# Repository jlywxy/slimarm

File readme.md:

# SlimARM Boards

The project is aiming to manufacture custom-made PCB of Embedded MPUs(most having ARM cores; specially-designed for specified usage, slim in dimension).<br>

Author: jlywxy(jlywxy@outlook.com)<br>
License: GPLv2<br>

- --

## Board List

<b>Important:</b><br>
Check `board/readme.PCB_DESIGN_STATUS.md` before actual PCB manufacture process. <br>Use verified boards only.
<br>
<br>
Status of Working Boards:
Code|Chipset|Core<br>DRAM Clock|PCB Stack<br>EDA|Status
-|-|-|-|-
Hypericum|Allwinner A20|1.2GHz 2x Cortex-A7<br>400MHz(800Mbps) DDR3|4-layer<br>KiCad|✅final-pcb
Carambola|Atmel AT91SAM9G25|400MHz ARM926EJ-S<br>133MHz(266Mbps) DDR2|4-layer<br>KiCad|✅final-pcb
Apricot B|Samsung S3C2416X|400MHz ARM926EJ-S<br>133MHz(266Mbps) DDR2|4-layer<br>LCEDA|pcb-revision
Almond B|Samsung S3C2410|200MHz ARM920T<br>133MHz SDR|4-layer<br>KiCAD|pcb-revision
||||
Azalea|Rockchip RK3128|1.1GHz 4x Cortex-A7<br>533MHz(1066Mbps)DDR3|4-layer<br>Cadence|pre-sch
Clematis|Rockchip RK3188|1.1GHz 4x Cortex-A9<br>533MHz(1066Mbps)DDR3|4-layer<br>KiCad|pre-sch
|Cumquat<br>(*SlimMIPS)|MediaTek MT7620A|580MHz MIPS24KEc<br>192MHz(384Mbps) DDR2|4-layer<br>KiCAD & Cadence(two versions)|pre-sch

Project Pipeline: planning -> avail-analyse -> pre-sch -> pcb-fab-test(1-stage pcb) -> software-test  -> post-sch -> pcb-revision -> post-pcb-fab-test -> final-pcb -> post-software-test -> done

- --
## Lastest Information
(this column started tracking from 2023.5.14)
* `Carambola`(AT91SAM9G25) the second version of hardware released and under test. Note: The first version failed for the wrong tuning of DDR lines. @ 2023.5.14
* `Apricot`(S3C2416) hardware final design finished with version/revision `v1r0x205`, the software for this board is under development @ 2023.5.17
* `Almond Mini`(S3C2410) hardware final design finished with version/revision `v1r1x208` @ 2023.5.20
* `Carambola` turning into a stall state for the unclear DDR2 initialization procedures of atmel mpus. @ 2023.5.26
* `Apricot` pushed new hardware version v1r1, which fixed UDEV clock input line and added pad teardrops. @ 2023.5.27
* added new plan for `Oxalis Mini` @ 2023.5.27
* cut down project plan with existing working plan. @ 2023.5.28
* `Apricot`(S3C2416) hardware debug is done, DDR2 initialization is ok. Starting USB 2.0 HS and Linux software debug. @ 2023.6.2
* corrected `Apricot` ddr clock information in project progress chart to 133 MHz. @ 2023.6.2
* dropped `Carambola`; starting `Oxalis Mini` schematic design. @ 2023.6.4
* revisioning `Carambola`; starting `Hypericum`. @ 2023.6.24
* `Hypericum`(a alias of `Oxalis Mini`)(Allwinner-A20) first board test done, revisioning; `Apricot`(S3C2416) third board(v1r3) test done, revisioning; `Carambola` board under test. @ 2023.7.2
* Fixed SDIO pull-up problem for `Hypericum`, `Carambola`, `Apricot` boards. @ 2023.7.11
* `Carambola` newest board tested done; needed to roll back to version that did not pulled up at SDIO, SAM9G25 have internal pull-up for SDIO.  @ 2023.7.15
* `Carambola`, `Hypericum` fixed with reset chip, SDIO pull-ups, ExtIO layout. These versions are verified and committed. @2023.7.22

## Misc
1. the version identifier on silkscreen of boards:<br>
(1)`v1r2e3` means version 1, revision 2, edition 3.<br>
typically written in `version 1.1.1`.<br>
(2)`v1r2x202` means version 1, revision 2, date May 14th.<br>
typically written in `version 1.1, 5.14`.<br>
these types of version identifiers are all used among boards.

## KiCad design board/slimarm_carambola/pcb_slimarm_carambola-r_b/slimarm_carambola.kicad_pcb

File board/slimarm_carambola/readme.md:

# SlimARM Carambola

## Recommended Software Test Procedure
1. DRAM test:<br>
* DDR controller set and DDR initialization.<br>
use AT91Bootstrap (version 3.x):<br>
(build binary)
```shell
$ cd /path/to/at91bootstrap/code
$ make mrproper
$ make core9g25-128m-nf_defconfig
$ CROSS_COMPILE=arm-none-eabi- make -j8
```
(do not use at91sam9x5ek configuration)
* DDR read/write stability test.<br>
use RAMStepper:<br>
(build binary)
```shell
$ cd /path/to/ramstepper
$ make clean
$ make carambola_config
```
this program writes to DDR SDRAM sequentially and reads out & compare data sequentially.

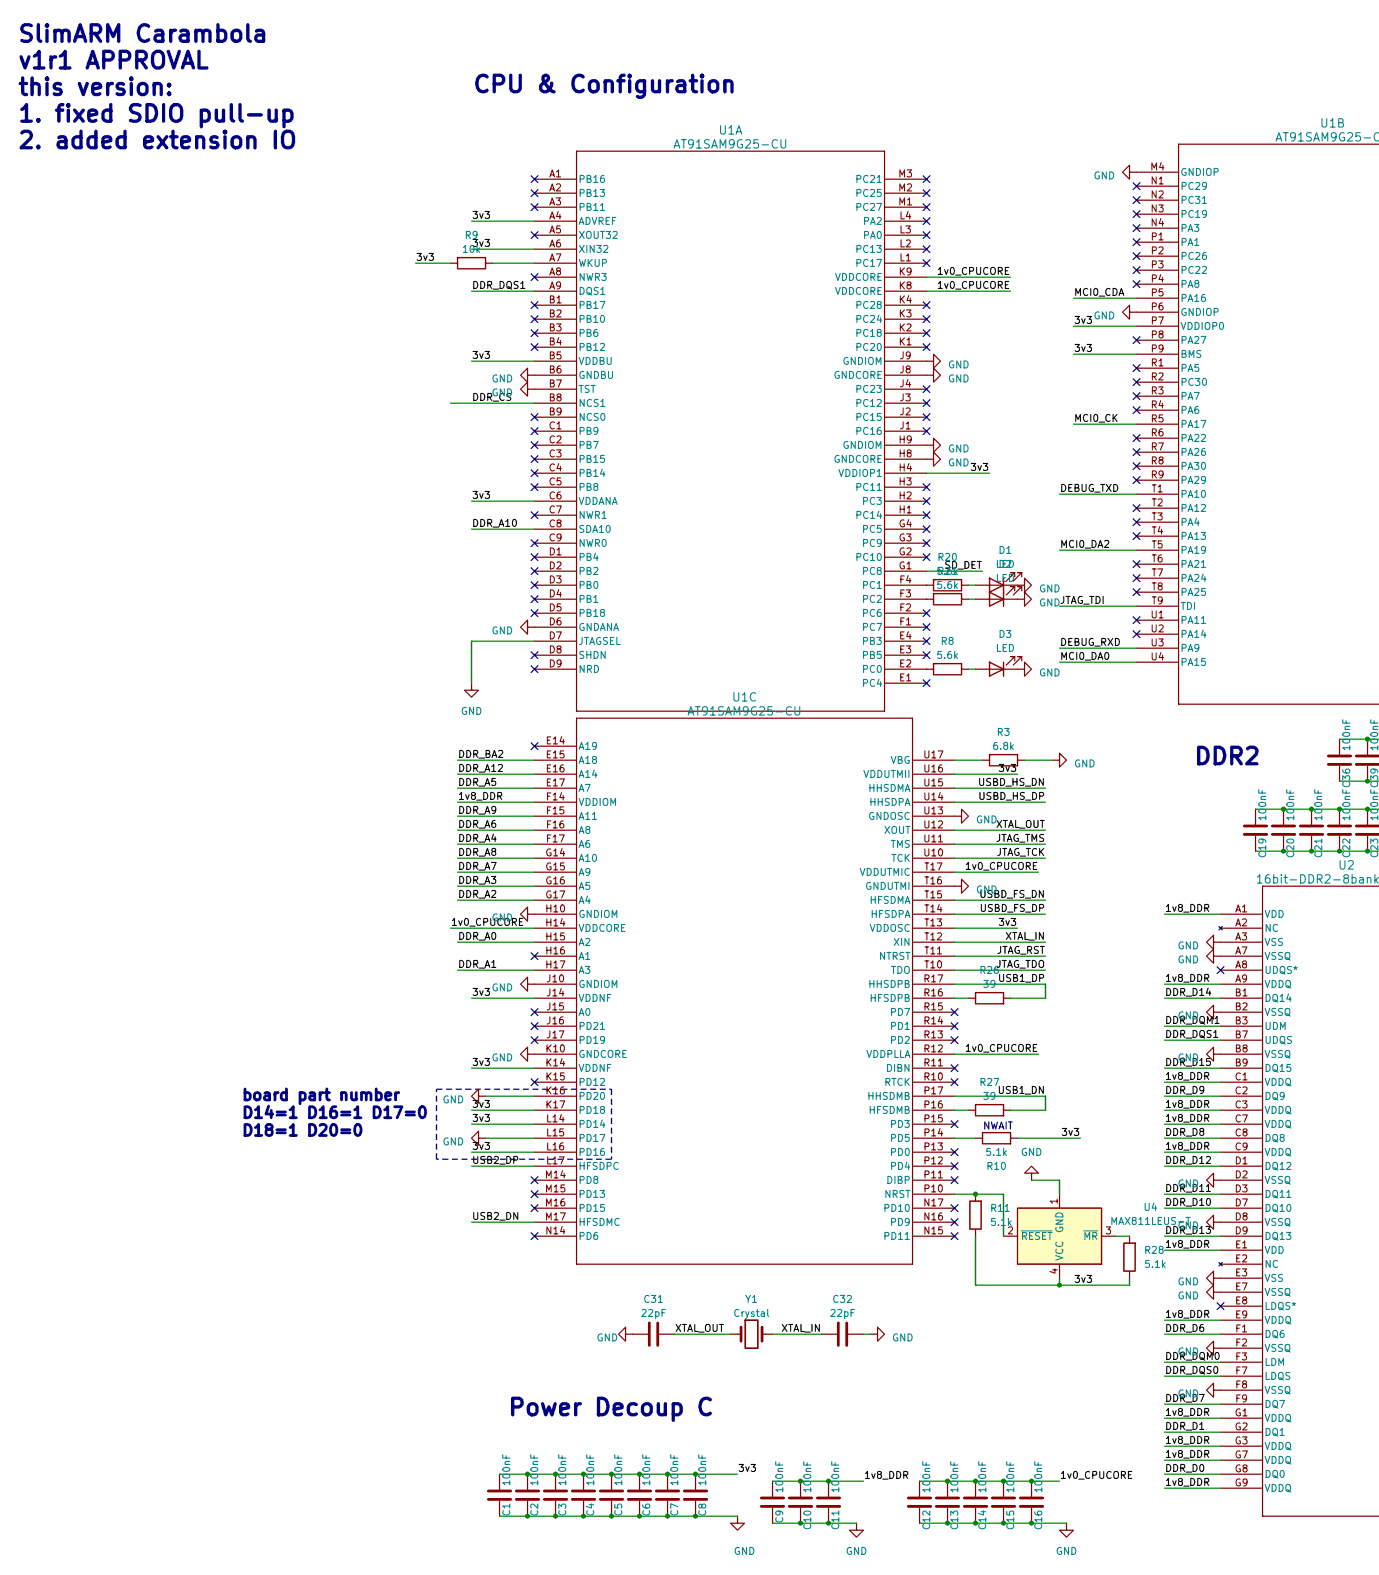
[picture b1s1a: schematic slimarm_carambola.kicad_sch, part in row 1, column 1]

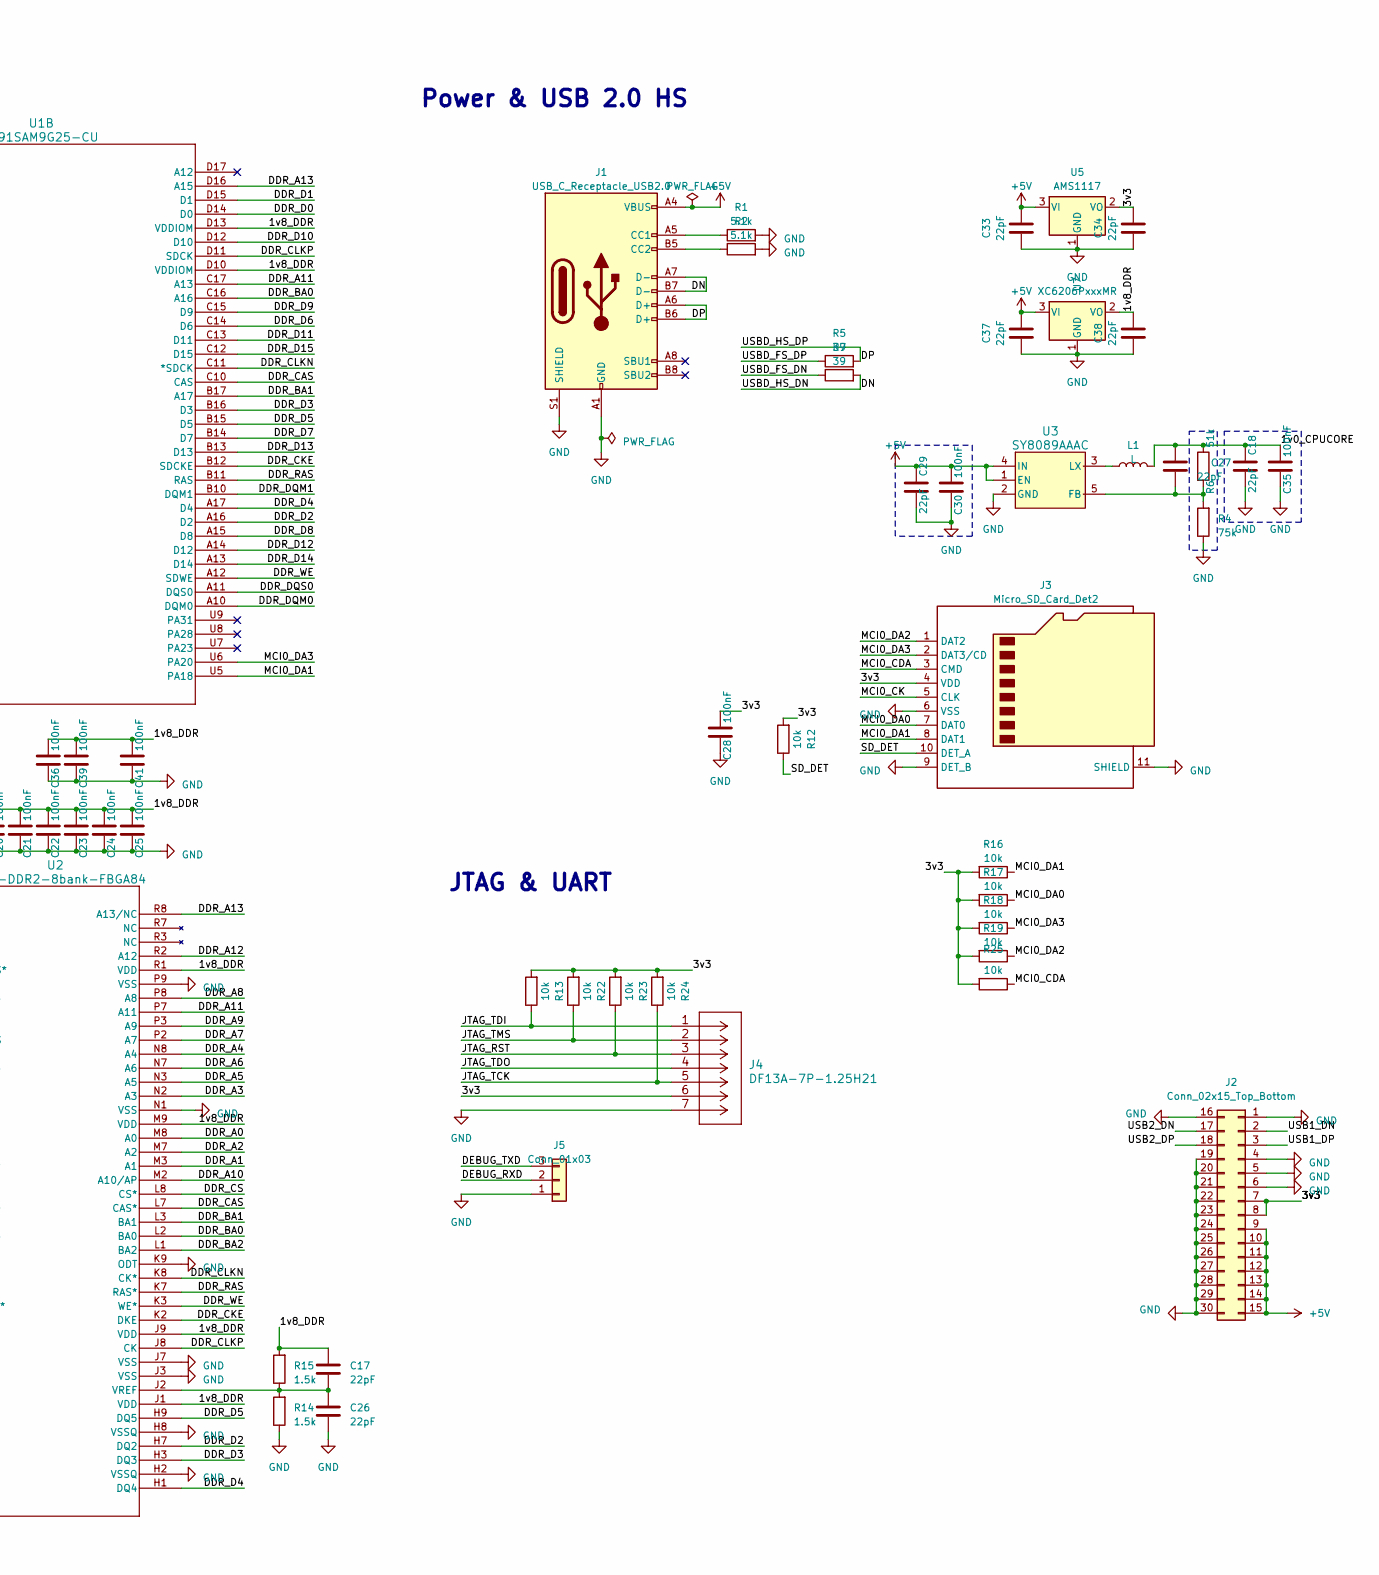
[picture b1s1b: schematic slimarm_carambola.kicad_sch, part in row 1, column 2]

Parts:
C1, C2, C3, C4, C5, C6, C7, C8, C9, C10, C11, C12, C13, C14, C15, C16, C19, C20, C21, C22, C23, C24, C25, C28, C30, C35, C36, C39, C41: 100nF; 0402
C17, C18, C26, C27, C29, C31, C32, C33, C34, C37, C38: 22pF; 0402
D1, D2, D3: LED; LED_0603_1608Metric_Pad1.05x0.95mm_HandSolder
J1: USB_C_Receptacle_USB2.0; USB_TYPEC_Receptacle
J2: Conn_02x15_Top_Bottom; Hirose_DF12_DF12E3.0-30DP-0.5V_2x15_P0.50mm_Vertical
J3: Micro_SD_Card_Det2; microSD_HC_Molex_104031-0811
J4: DF13A-7P-1.25H21
J5: Conn_01x03; PinHeader_1x03_P2.54mm_Vertical
L1: L; L_Sunlord_SWPA3015S
R1, R2, R10, R11, R28: 5.1k; 0402
R3: 6.8k; 0603
R4: 75k; 0603
R5, R7, R26, R27: 39; 0603
R6: 51k; 0603
R8, R20, R21: 5.6k; 0603
R9, R12, R13, R16, R17, R18, R19, R22, R23, R24, R25: 10k; 0402
R14, R15: 1.5k; 0603
U1: AT91SAM9G25-CU; AT91SAM9G25_JKT
U2: 16bit-DDR2-8bank-FBGA84; BGA84_DDR2
U3: SY8089AAAC; SY8089
U4: MAX811LEUS-T; SOT-143
U5: AMS1117; SOT-89-3
U7: XC6206PxxxMR; SOT-89-3
Y1: Crystal; Crystal_SMD_5032-2Pin_5.0x3.2mm

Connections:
+5V: C29.1, C30.2, C33.2, C37.2, J1.A4 (VBUS), J1.A9 (VBUS), J1.B4 (VBUS), J1.B9 (VBUS), J2.9, J2.10, J2.11, J2.12, J2.13, J2.14, J2.15, U3.1 (EN), U3.4 (IN), U5.3 (VI), U7.3 (VI)
/1v0_CPUCORE: C12.2, C13.2, C14.2, C15.2, C16.2, C18.1, C27.1, C35.2, L1.2, R6.1, U1.H14 (VDDCORE), U1.K8 (VDDCORE), U1.K9 (VDDCORE), U1.R12 (VDDPLLA), U1.T17 (VDDUTMIC)
/1v8_DDR: C9.2, C10.2, C11.2, C17.2, C19.2, C20.2, C21.2, C22.2, C23.2, C24.2, C25.2, C36.2, C38.2, C39.2, C41.2, R15.2, U1.D10 (VDDIOM), U1.D13 (VDDIOM), U1.F14 (VDDIOM), U2.A1 (VDD), U2.A9 (VDDQ), U2.C1 (VDDQ), U2.C3 (VDDQ), U2.C7 (VDDQ), U2.C9 (VDDQ), U2.E1 (VDD), U2.E9 (VDDQ), U2.G1 (VDDQ), U2.G3 (VDDQ), U2.G7 (VDDQ), U2.G9 (VDDQ), U2.J1 (VDD), U2.J9 (VDD), U2.M9 (VDD), U2.R1 (VDD), U7.2 (VO)
/3v3: C1.2, C2.2, C3.2, C4.2, C5.2, C6.2, C7.2, C8.2, C28.2, C34.2, J2.7, J2.8, J3.4 (VDD), J4.6, R9.2, R10.2, R11.1, R12.2, R13.2, R16.2, R17.2, R18.2, R19.2, R22.2, R23.2, R24.2, R25.2, R28.1, U1.A4 (ADVREF), U1.A6 (XIN32), U1.B5 (VDDBU), U1.C6 (VDDANA), U1.H4 (VDDIOP1), U1.J14 (VDDNF), U1.K14 (VDDNF), U1.K17 (PD18), U1.L14 (PD14), U1.L16 (PD16), U1.P7 (VDDIOP0), U1.P9 (BMS), U1.T13 (VDDOSC), U1.U16 (VDDUTMII), U4.4 (VCC), U5.2 (VO)
/DDR_A0: U1.H15 (A2), U2.M8 (A0)
/DDR_A1: U1.H17 (A3), U2.M3 (A1)
/DDR_A2: U1.G17 (A4), U2.M7 (A2)
/DDR_A3: U1.G16 (A5), U2.N2 (A3)
/DDR_A4: U1.F17 (A6), U2.N8 (A4)
/DDR_A5: U1.E17 (A7), U2.N3 (A5)
/DDR_A6: U1.F16 (A8), U2.N7 (A6)
/DDR_A7: U1.G15 (A9), U2.P2 (A7)
/DDR_A8: U1.G14 (A10), U2.P8 (A8)
/DDR_A9: U1.F15 (A11), U2.P3 (A9)
/DDR_A10: U1.C8 (SDA10), U2.M2 (A10/AP)
/DDR_A11: U1.C17 (A13), U2.P7 (A11)
/DDR_A12: U1.E16 (A14), U2.R2 (A12)
/DDR_A13: U1.D16 (A15), U2.R8 (A13/NC)
/DDR_BA0: U1.C16 (A16), U2.L2 (BA0)
/DDR_BA1: U1.B17 (A17), U2.L3 (BA1)
/DDR_BA2: U1.E15 (A18), U2.L1 (BA2)
/DDR_CAS: U1.C10 (CAS), U2.L7 (CAS*)
/DDR_CKE: U1.B12 (SDCKE), U2.K2 (DKE)
/DDR_CLKN: U1.C11 (*SDCK), U2.K8 (CK*)
/DDR_CLKP: U1.D11 (SDCK), U2.J8 (CK)
/DDR_CS: U1.B8 (NCS1), U2.L8 (CS*)
/DDR_D0: U1.D14 (D0), U2.G8 (DQ0)
/DDR_D1: U1.D15 (D1), U2.G2 (DQ1)
/DDR_D2: U1.A16 (D2), U2.H7 (DQ2)
/DDR_D3: U1.B16 (D3), U2.H3 (DQ3)
/DDR_D4: U1.A17 (D4), U2.H1 (DQ4)
/DDR_D5: U1.B15 (D5), U2.H9 (DQ5)
/DDR_D6: U1.C14 (D6), U2.F1 (DQ6)
/DDR_D7: U1.B14 (D7), U2.F9 (DQ7)
/DDR_D8: U1.A15 (D8), U2.C8 (DQ8)
/DDR_D9: U1.C15 (D9), U2.C2 (DQ9)
/DDR_D10: U1.D12 (D10), U2.D7 (DQ10)
/DDR_D11: U1.C13 (D11), U2.D3 (DQ11)
/DDR_D12: U1.A14 (D12), U2.D1 (DQ12)
/DDR_D13: U1.B13 (D13), U2.D9 (DQ13)
/DDR_D14: U1.A13 (D14), U2.B1 (DQ14)
/DDR_D15: U1.C12 (D15), U2.B9 (DQ15)
/DDR_DQM0: U1.A10 (DQM0), U2.F3 (LDM)
/DDR_DQM1: U1.B10 (DQM1), U2.B3 (UDM)
/DDR_DQS0: U1.A11 (DQS0), U2.F7 (LDQS)
/DDR_DQS1: U1.A9 (DQS1), U2.B7 (UDQS)
/DDR_RAS: U1.B11 (RAS), U2.K7 (RAS*)
/DDR_WE: U1.A12 (SDWE), U2.K3 (WE*)
/DEBUG_RXD: J5.2, U1.U3 (PA9)
/DEBUG_TXD: J5.3, U1.T1 (PA10)
/DN: J1.A7 (D-), J1.B7 (D-), R7.2, U1.U15 (HHSDMA)
/DP: J1.A6 (D+), J1.B6 (D+), R5.2, U1.U14 (HHSDPA)
/JTAG_RST: J4.3, R23.1, U1.T11 (NTRST)
/JTAG_TCK: J4.5, R24.1, U1.U10 (TCK)
/JTAG_TDI: J4.1, R13.1, U1.T9 (TDI)
/JTAG_TDO: J4.4, U1.T10 (TDO)
/JTAG_TMS: J4.2, R22.1, U1.U11 (TMS)
/MCI0_CDA: J3.3 (CMD), R25.1, U1.P5 (PA16)
/MCI0_CK: J3.5 (CLK), U1.R5 (PA17)
/MCI0_DA0: J3.7 (DAT0), R17.1, U1.U4 (PA15)
/MCI0_DA1: J3.8 (DAT1), R16.1, U1.U5 (PA18)
/MCI0_DA2: J3.1 (DAT2), R19.1, U1.T5 (PA19)
/MCI0_DA3: J3.2 (DAT3/CD), R18.1, U1.U6 (PA20)
/SD_DET: J3.10 (DET_A), R12.1, U1.G1 (PC8)
/USB1_DN: J2.2, R27.2, U1.P17 (HHSDMB)
/USB1_DP: J2.3, R26.2, U1.R17 (HHSDPB)
/USB2_DN: J2.17, U1.M17 (HFSDMC)
/USB2_DP: J2.18, U1.L17 (HFSDPC)
/USBD_FS_DN: R7.1, U1.T15 (HFSDMA)
/USBD_FS_DP: R5.1, U1.T14 (HFSDPA)
/XTAL_IN: C32.1, U1.T12 (XIN), Y1.2
/XTAL_OUT: C31.2, U1.U12 (XOUT), Y1.1
GND: C1.1, C2.1, C3.1, C4.1, C5.1, C6.1, C7.1, C8.1, C9.1, C10.1, C11.1, C12.1, C13.1, C14.1, C15.1, C16.1, C18.2, C19.1, C20.1, C21.1, C22.1, C23.1, C24.1, C25.1, C26.1, C28.1, C29.2, C30.1, C31.1, C32.2, C33.1, C34.1, C35.1, C36.1, C37.1, C38.1, C39.1, C41.1, D1.1 (K), D2.1 (K), D3.1 (K), J1.A1 (GND), J1.A12 (GND), J1.B1 (GND), J1.B12 (GND), J1.S1 (SHIELD), J2.1, J2.4, J2.5, J2.6, J2.16, J2.19, J2.20, J2.21, J2.22, J2.23, J2.24, J2.25, J2.26, J2.27, J2.28, J2.29, J2.30, J3.6 (VSS), J3.9 (DET_B), J3.11 (SHIELD), J4.7, J5.1, R1.2, R2.2, R3.1, R4.1, R14.1, U1.B6 (GNDBU), U1.B7 (TST), U1.D6 (GNDANA), U1.D7 (JTAGSEL), U1.H8 (GNDCORE), U1.H9 (GNDIOM), U1.H10 (GNDIOM), U1.J8 (GNDCORE), U1.J9 (GNDIOM), U1.J10 (GNDIOM), U1.K10 (GNDCORE), U1.K16 (PD20), U1.L15 (PD17), U1.M4 (GNDIOP), U1.P6 (GNDIOP), U1.T16 (GNDUTMI), U1.U13 (GNDOSC), U2.A3 (VSS), U2.A7 (VSSQ), U2.B2 (VSSQ), U2.B8 (VSSQ), U2.D2 (VSSQ), U2.D8 (VSSQ), U2.E3 (VSS), U2.E7 (VSSQ), U2.F2 (VSSQ), U2.F8 (VSSQ), U2.H2 (VSSQ), U2.H8 (VSSQ), U2.J3 (VSS), U2.J7 (VSS), U2.K9 (ODT), U2.N1 (VSS), U2.P9 (VSS), U3.2 (GND), U4.1 (GND), U5.1 (GND), U7.1 (GND)
unnamed: D1.2 (A), R20.1
unnamed: D2.2 (A), R21.1
unnamed: D3.2 (A), R8.1
unnamed: J1.A5 (CC1), R1.1
unnamed: J1.B5 (CC2), R2.1
unnamed: R8.2, U1.E2 (PC0)
unnamed: R20.2, U1.F4 (PC1)
unnamed: R21.2, U1.F3 (PC2)
unnamed: R9.1, U1.A7 (WKUP)
unnamed: R27.1, U1.P16 (HFSDMB)
unnamed: R26.1, U1.R16 (HFSDPB)
unnamed: R11.2, U1.P10 (NRST), U4.2 (~RESET)
unnamed: R10.1, U1.P14 (PD5)
unnamed: R3.2, U1.U17 (VBG)
unnamed: C17.1, C26.2, R14.2, R15.1, U2.J2 (VREF)
unnamed: C27.2, R4.2, R6.2, U3.5 (FB)
unnamed: L1.1, U3.3 (LX)
unnamed: R28.2, U4.3 (~MR)

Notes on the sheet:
CPU & Configuration
NWAIT
SlimARM Carambola v1r1 APPROVAL this version: 1. fixed SDIO pull-up 2. added extension IO
Power & USB 2.0 HS
JTAG & UART
DDR2
Power Decoup C
board part number D14=1 D16=1 D17=0 D18=1 D20=0

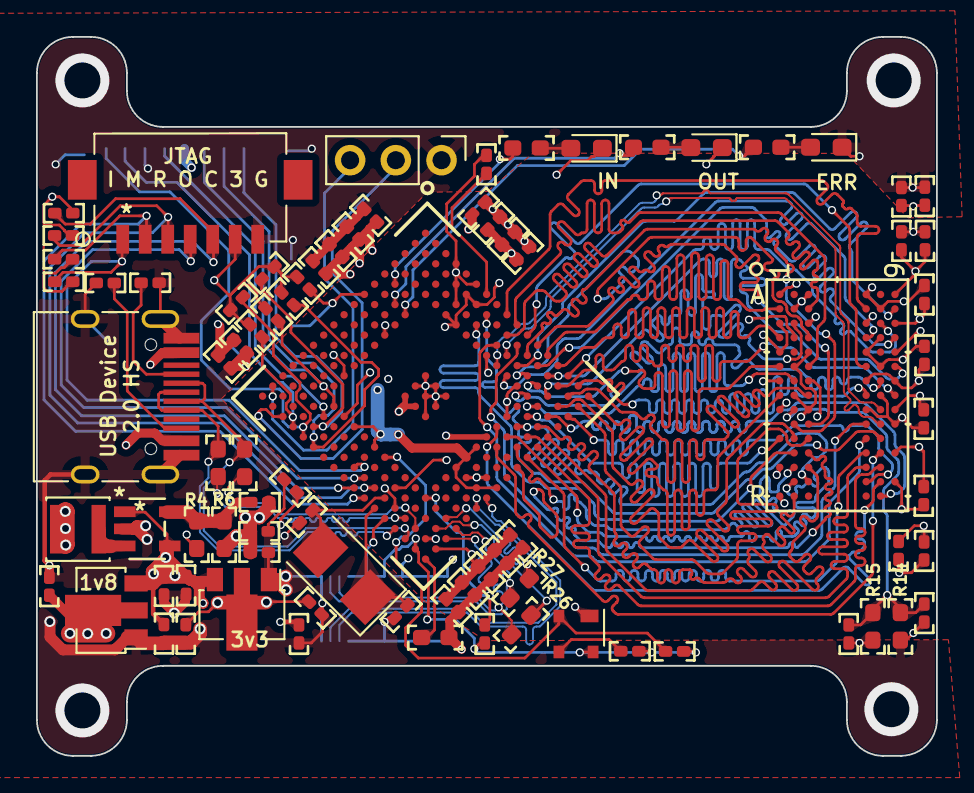
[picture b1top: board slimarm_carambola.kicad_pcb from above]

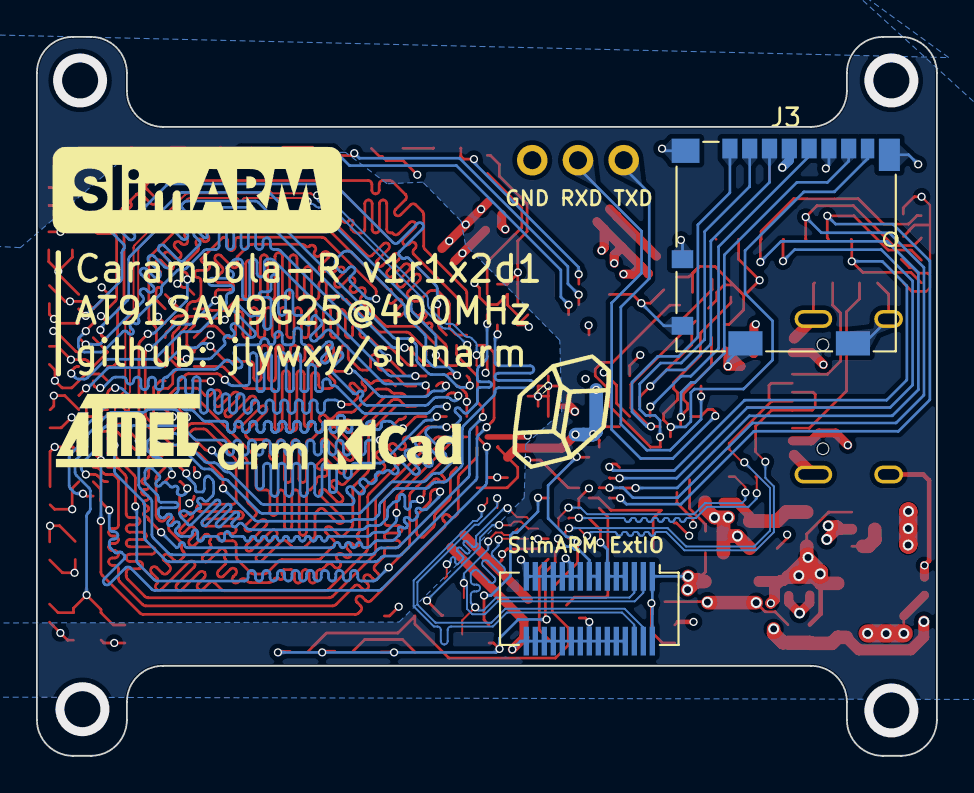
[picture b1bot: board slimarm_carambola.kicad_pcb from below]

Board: 4 copper layers, 50.0 x 39.9 mm, 84 parts (2 on the bottom side), 91 nets.

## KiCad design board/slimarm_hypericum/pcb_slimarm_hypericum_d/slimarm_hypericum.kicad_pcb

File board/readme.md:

# Boards

Project status:<br>
```
[ok]SlimARM Almond Mini(S3C2410)
[working]SlimARM Apricot(S3C2416)
[stalled]SlimARM Carambola(AT91SAM9G25)
[planning]SlimARM Oxalis Mini(A20)
[planning]SlimMIPS Cumquat(MT7620)
```

- --
## Misc

### Document Patch and Errata
* Marked slimarm classic 2410 workaround state.
* Paused the process of part "slimarm classic 2416" due to PCB manufacturing problem taken by 0.65mm-pitch BGA design.<br>

patch above: jlywxy@2023.3.11<br>

* using new naming method for boards.
* Adding new board of S3C2416 and AT91SAM9G25 SoCs.

patch above: jlywxy@2023.5.20<br>

* Adding new board of A20 and MT7620 SoCs.
* Marked `Carambola` stall state.

patch above: jlywxy@2023.5.27<br>

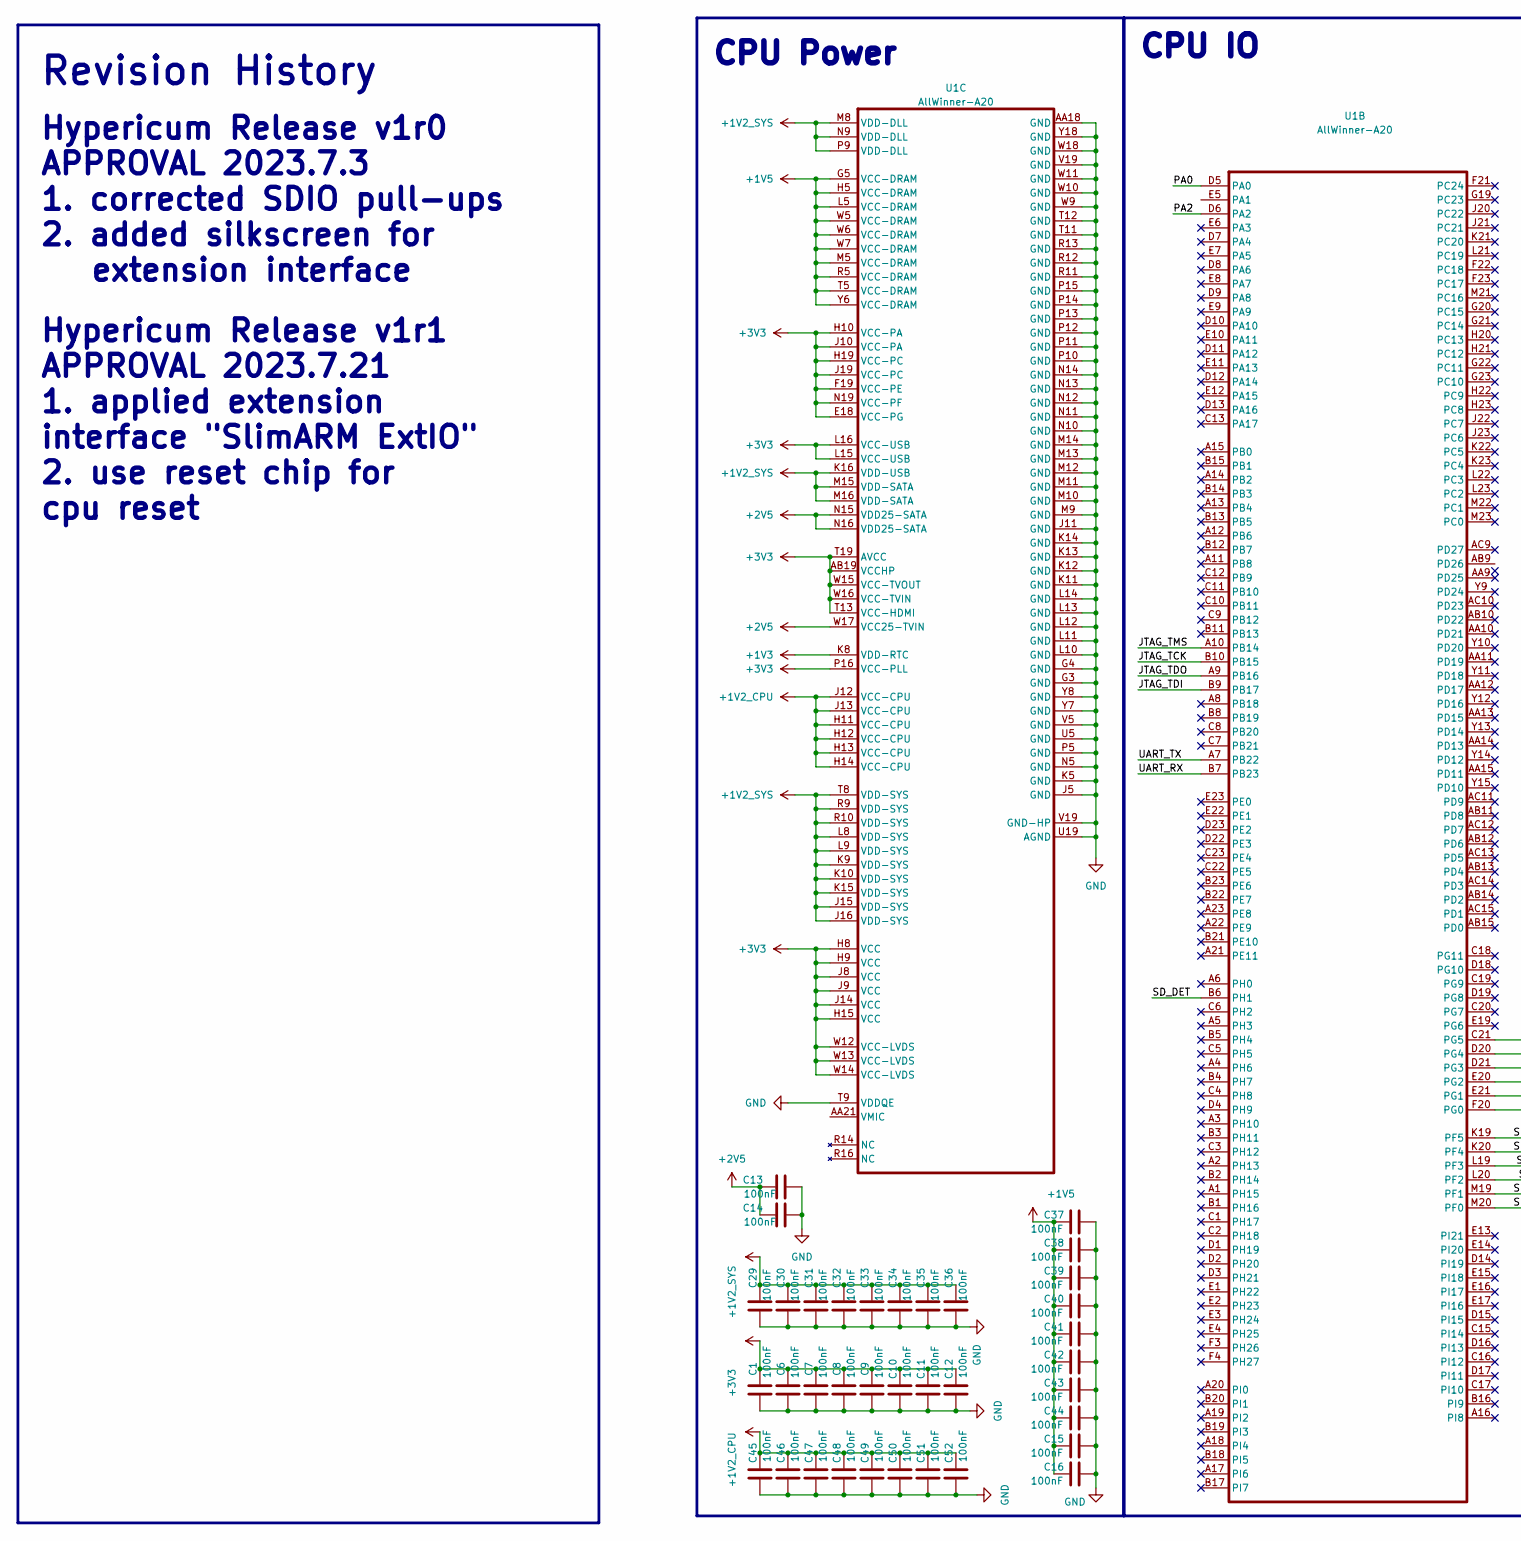
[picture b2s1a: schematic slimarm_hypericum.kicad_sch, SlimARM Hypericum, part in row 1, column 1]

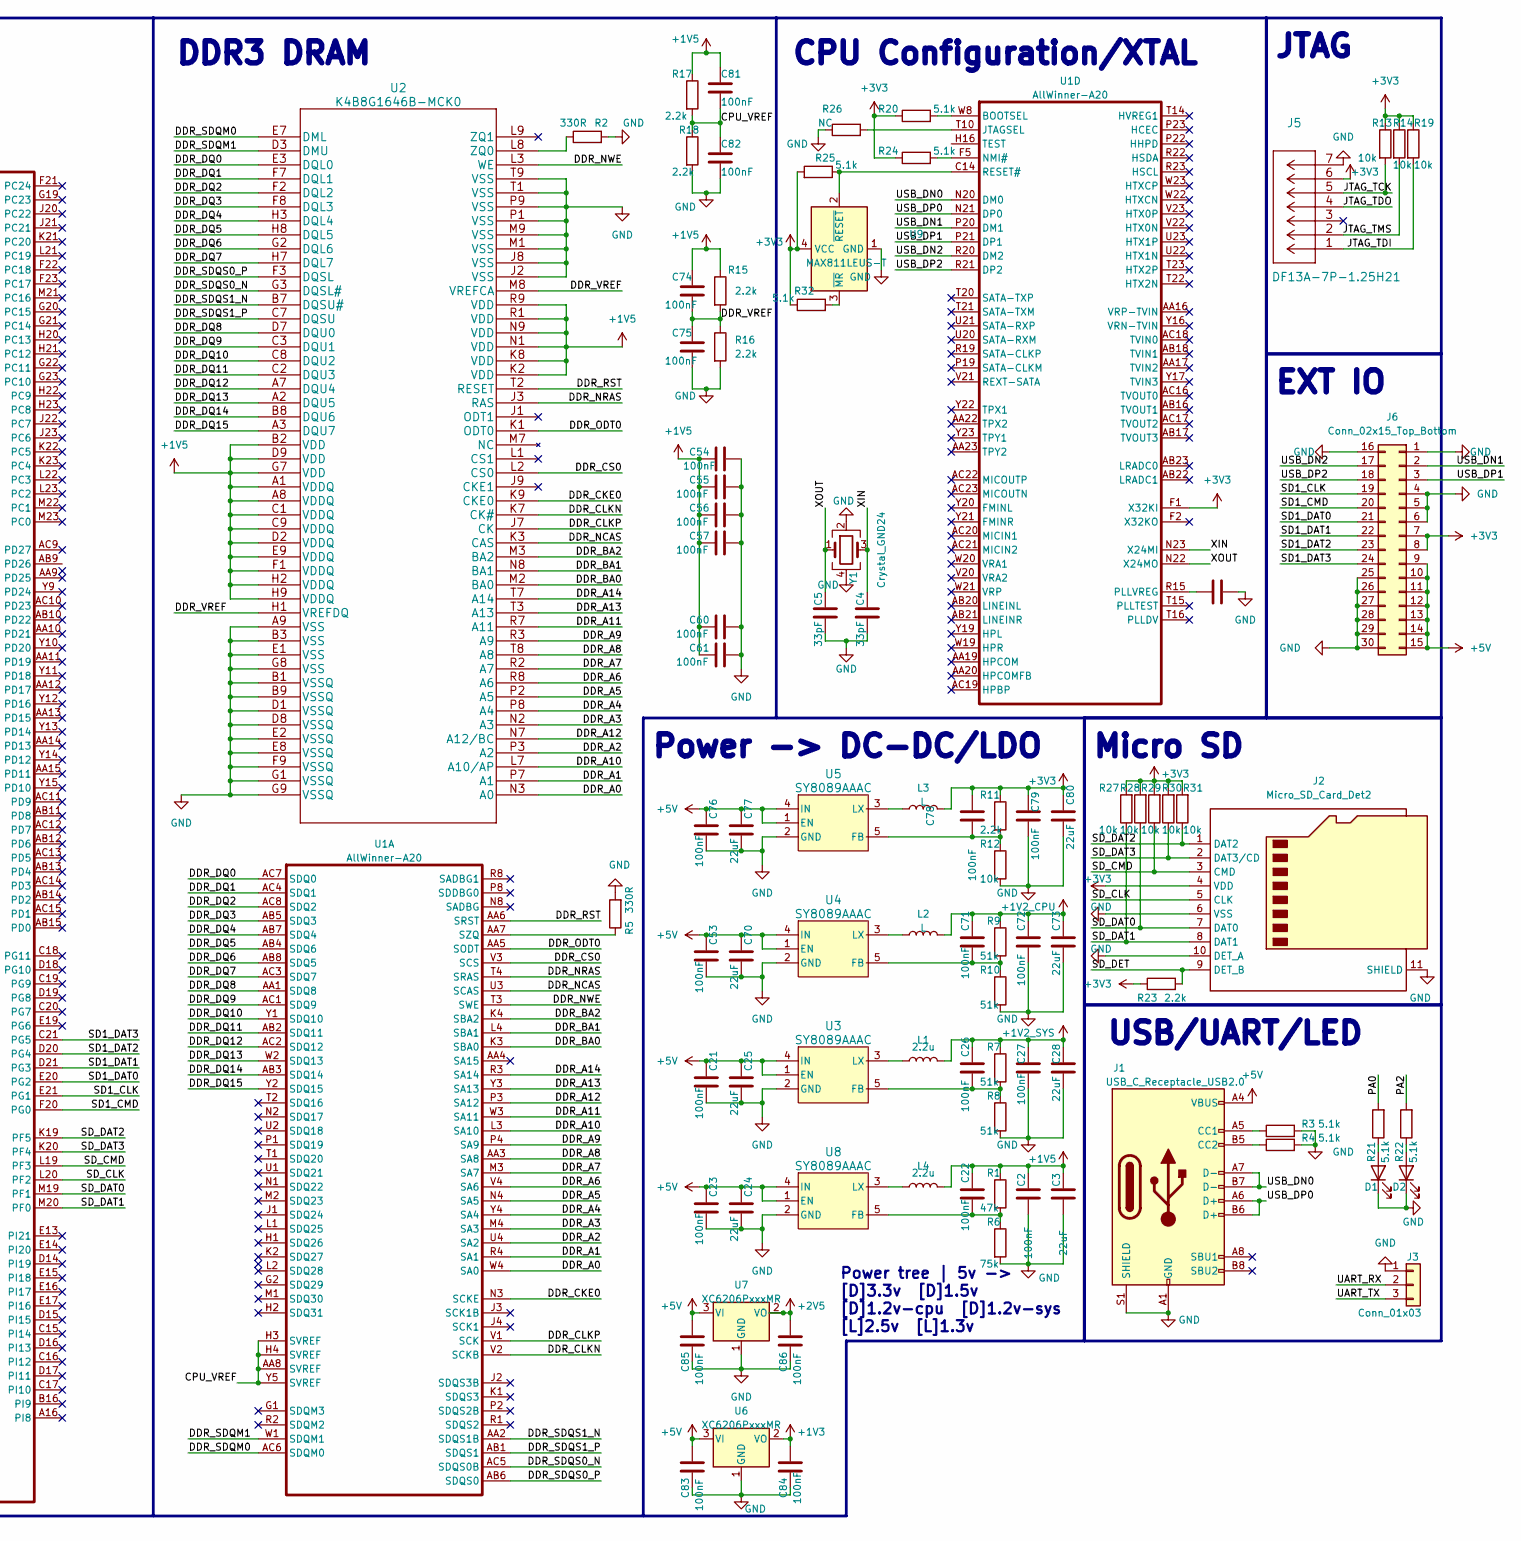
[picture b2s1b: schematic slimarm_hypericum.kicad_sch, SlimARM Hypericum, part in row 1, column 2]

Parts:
C1, C2, C6, C7, C8, C9, C10, C11, C12, C13, C14, C15, C16, C21, C22, C23, C26, C27, C29, C30, C31, C32, C33, C34, C35, C36, C37, C38, C39, C40, C41, C42, C43, C44, C45, C46, C47, C48, C49, C50, C51, C52, C53, C54, C55, C56, C57, C60, C61, C71, C72, C74, C75, C76, C78, C79, C81, C82, C83, C84, C85, C86: 100nF; 0402
C3, C24, C25, C28, C70, C73, C77, C80: 22uF; 0402
C4, C5, C17: 33pF; 0402
D1, D2: LED; LED_0603_1608Metric_Pad1.05x0.95mm_HandSolder
J1: USB_C_Receptacle_USB2.0; USB_TYPEC_Receptacle
J2: Micro_SD_Card_Det2; microSD_HC_Molex_104031-0811
J3: Conn_01x03; PinHeader_1x03_P2.54mm_Vertical
J5: DF13A-7P-1.25H21
J6: Conn_02x15_Top_Bottom; Hirose_DF12_DF12C3.0-30DS-0.5V_2x15_P0.50mm_Vertical
L1, L4: 2.2u; L_Sunlord_SWPA3015S
L2, L3: L; L_Sunlord_SWPA3015S
R1: 47k; 0603
R2, R5: 330R; 0603
R3, R4, R20, R21, R22, R24, R25, R32: 5.1k; 0402
R6: 75k; 0603
R7, R8, R9, R10: 51k; 0603
R11, R15, R16, R17, R18: 2.2k; 0603
R12: 10k; 0603
R13, R14, R19, R27, R28, R29, R30, R31: 10k; 0402
R23: 2.2k; 0402
R26: NC; 0402
U1: AllWinner-A20; awa20
U2: K4B8G1646B-MCK0
U3, U4, U5, U8: SY8089AAAC; SY8089
U6, U7: XC6206PxxxMR; SOT-23-3
U9: MAX811LEUS-T; SOT-143
Y1: Crystal_GND24; Crystal_SMD_3225-4Pin_3.2x2.5mm

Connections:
+1V2_CPU: C45.1, C46.1, C47.1, C48.1, C49.1, C50.1, C51.1, C52.1, C71.2, C72.2, C73.2, L2.2, R9.1, U1.H11 (VCC-CPU), U1.H12 (VCC-CPU), U1.H13 (VCC-CPU), U1.H14 (VCC-CPU), U1.J12 (VCC-CPU), U1.J13 (VCC-CPU)
+1V2_SYS: C26.2, C27.2, C28.2, C29.1, C30.1, C31.1, C32.1, C33.1, C34.1, C35.1, C36.1, L1.2, R7.1, U1.J15 (VDD-SYS), U1.J16 (VDD-SYS), U1.K9 (VDD-SYS), U1.K10 (VDD-SYS), U1.K15 (VDD-SYS), U1.K16 (VDD-USB), U1.L8 (VDD-SYS), U1.L9 (VDD-SYS), U1.M8 (VDD-DLL), U1.M15 (VDD-SATA), U1.M16 (VDD-SATA), U1.N9 (VDD-DLL), U1.P9 (VDD-DLL), U1.R9 (VDD-SYS), U1.R10 (VDD-SYS), U1.T8 (VDD-SYS)
+1V3: C84.2, U1.K8 (VDD-RTC), U6.2 (VO)
+1V5: C2.2, C3.2, C15.1, C16.1, C22.2, C37.1, C38.1, C39.1, C40.1, C41.1, C42.1, C43.1, C44.1, C54.1, C55.1, C56.1, C57.1, C60.1, C61.1, C74.2, C81.2, L4.2, R1.1, R15.1, R17.1, U1.G5 (VCC-DRAM), U1.H5 (VCC-DRAM), U1.L5 (VCC-DRAM), U1.M5 (VCC-DRAM), U1.R5 (VCC-DRAM), U1.T5 (VCC-DRAM), U1.W5 (VCC-DRAM), U1.W6 (VCC-DRAM), U1.W7 (VCC-DRAM), U1.Y6 (VCC-DRAM), U2.A1 (VDDQ), U2.A8 (VDDQ), U2.B2 (VDD), U2.C1 (VDDQ), U2.C9 (VDDQ), U2.D2 (VDDQ), U2.D9 (VDD), U2.E9 (VDDQ), U2.F1 (VDDQ), U2.G7 (VDD), U2.H2 (VDDQ), U2.H9 (VDDQ), U2.K2 (VDD), U2.K8 (VDD), U2.N1 (VDD), U2.N9 (VDD), U2.R1 (VDD), U2.R9 (VDD)
+2V5: C13.1, C14.1, C86.2, U1.N15 (VDD25-SATA), U1.N16 (VDD25-SATA), U1.W17 (VCC25-TVIN), U7.2 (VO)
+3V3: C1.1, C6.1, C7.1, C8.1, C9.1, C10.1, C11.1, C12.1, C78.2, C79.2, C80.2, J2.4 (VDD), J5.6, J6.7, J6.8, L3.2, R11.1, R13.1, R14.1, R19.1, R20.1, R23.1, R24.1, R25.2, R27.2, R28.2, R29.2, R30.2, R31.2, R32.1, U1.AB19 (VCCHP), U1.E18 (VCC-PG), U1.F1 (X32KI), U1.F19 (VCC-PE), U1.H8 (VCC), U1.H9 (VCC), U1.H10 (VCC-PA), U1.H15 (VCC), U1.H19 (VCC-PC), U1.J8 (VCC), U1.J9 (VCC), U1.J10 (VCC-PA), U1.J14 (VCC), U1.J19 (VCC-PC), U1.L15 (VCC-USB), U1.L16 (VCC-USB), U1.N19 (VCC-PF), U1.P16 (VCC-PLL), U1.T13 (VCC-HDMI), U1.T19 (AVCC), U1.W12 (VCC-LVDS), U1.W13 (VCC-LVDS), U1.W14 (VCC-LVDS), U1.W15 (VCC-TVOUT), U1.W16 (VCC-TVIN), U9.4 (VCC)
+5V: C21.2, C23.2, C24.2, C25.2, C53.2, C70.2, C76.2, C77.2, C83.2, C85.2, J1.A4 (VBUS), J1.A9 (VBUS), J1.B4 (VBUS), J1.B9 (VBUS), J6.9, J6.10, J6.11, J6.12, J6.13, J6.14, J6.15, U3.1 (EN), U3.4 (IN), U4.1 (EN), U4.4 (IN), U5.1 (EN), U5.4 (IN), U6.3 (VI), U7.3 (VI), U8.1 (EN), U8.4 (IN)
/CPU_VREF: C81.1, C82.2, R17.2, R18.1, U1.AA8 (SVREF), U1.H3 (SVREF), U1.H4 (SVREF), U1.Y5 (SVREF)
/DDR_A0: U1.W4 (SA0), U2.N3 (A0)
/DDR_A1: U1.R4 (SA1), U2.P7 (A1)
/DDR_A2: U1.U4 (SA2), U2.P3 (A2)
/DDR_A3: U1.M4 (SA3), U2.N2 (A3)
/DDR_A4: U1.Y4 (SA4), U2.P8 (A4)
/DDR_A5: U1.N4 (SA5), U2.P2 (A5)
/DDR_A6: U1.V4 (SA6), U2.R8 (A6)
/DDR_A7: U1.M3 (SA7), U2.R2 (A7)
/DDR_A8: U1.AA3 (SA8), U2.T8 (A8)
/DDR_A9: U1.P4 (SA9), U2.R3 (A9)
/DDR_A10: U1.L3 (SA10), U2.L7 (A10/AP)
/DDR_A11: U1.W3 (SA11), U2.R7 (A11)
/DDR_A12: U1.P3 (SA12), U2.N7 (A12/BC)
/DDR_A13: U1.Y3 (SA13), U2.T3 (A13)
/DDR_A14: U1.R3 (SA14), U2.T7 (A14)
/DDR_BA0: U1.K3 (SBA0), U2.M2 (BA0)
/DDR_BA1: U1.L4 (SBA1), U2.N8 (BA1)
/DDR_BA2: U1.K4 (SBA2), U2.M3 (BA2)
/DDR_CKE0: U1.N3 (SCKE), U2.K9 (CKE0)
/DDR_CLKN: U1.V2 (SCKB), U2.K7 (CK#)
/DDR_CLKP: U1.V1 (SCK), U2.J7 (CK)
/DDR_CS0: U1.V3 (SCS), U2.L2 (CS0)
/DDR_DQ0: U1.AC7 (SDQ0), U2.E3 (DQL0)
/DDR_DQ1: U1.AC4 (SDQ1), U2.F7 (DQL1)
/DDR_DQ2: U1.AC8 (SDQ2), U2.F2 (DQL2)
/DDR_DQ3: U1.AB5 (SDQ3), U2.F8 (DQL3)
/DDR_DQ4: U1.AB7 (SDQ4), U2.H3 (DQL4)
/DDR_DQ5: U1.AB4 (SDQ6), U2.H8 (DQL5)
/DDR_DQ6: U1.AB8 (SDQ5), U2.G2 (DQL6)
/DDR_DQ7: U1.AC3 (SDQ7), U2.H7 (DQL7)
/DDR_DQ8: U1.AA1 (SDQ8), U2.D7 (DQU0)
/DDR_DQ9: U1.AC1 (SDQ9), U2.C3 (DQU1)
/DDR_DQ10: U1.Y1 (SDQ10), U2.C8 (DQU2)
/DDR_DQ11: U1.AB2 (SDQ11), U2.C2 (DQU3)
/DDR_DQ12: U1.AC2 (SDQ12), U2.A7 (DQU4)
/DDR_DQ13: U1.W2 (SDQ13), U2.A2 (DQU5)
/DDR_DQ14: U1.AB3 (SDQ14), U2.B8 (DQU6)
/DDR_DQ15: U1.Y2 (SDQ15), U2.A3 (DQU7)
/DDR_NCAS: U1.U3 (SCAS), U2.K3 (CAS)
/DDR_NRAS: U1.T4 (SRAS), U2.J3 (RAS)
/DDR_NWE: U1.T3 (SWE), U2.L3 (WE)
/DDR_ODT0: U1.AA5 (SODT), U2.K1 (ODT0)
/DDR_RST: U1.AA6 (SRST), U2.T2 (RESET)
/DDR_SDQM0: U1.AC6 (SDQM0), U2.E7 (DML)
/DDR_SDQM1: U1.W1 (SDQM1), U2.D3 (DMU)
/DDR_SDQS0_N: U1.AC5 (SDQS0B), U2.G3 (DQSL#)
/DDR_SDQS0_P: U1.AB6 (SDQS0), U2.F3 (DQSL)
/DDR_SDQS1_N: U1.AA2 (SDQS1B), U2.B7 (DQSU#)
/DDR_SDQS1_P: U1.AB1 (SDQS1), U2.C7 (DQSU)
/DDR_VREF: C74.1, C75.2, R15.2, R16.1, U2.H1 (VREFDQ), U2.M8 (VREFCA)
/JTAG_TCK: J5.5, R13.2, U1.B10 (PB15)
/JTAG_TDI: J5.1, R19.2, U1.B9 (PB17)
/JTAG_TDO: J5.4, U1.A9 (PB16)
/JTAG_TMS: J5.2, R14.2, U1.A10 (PB14)
/PA0: R21.2, U1.D5 (PA0)
/PA2: R22.2, U1.D6 (PA2)
/SD1_CLK: J6.19, U1.E21 (PG1)
/SD1_CMD: J6.20, U1.F20 (PG0)
/SD1_DAT0: J6.21, U1.E20 (PG2)
/SD1_DAT1: J6.22, U1.D21 (PG3)
/SD1_DAT2: J6.23, U1.D20 (PG4)
/SD1_DAT3: J6.24, U1.C21 (PG5)
/SD_CLK: J2.5 (CLK), U1.L20 (PF2)
/SD_CMD: J2.3 (CMD), R29.1, U1.L19 (PF3)
/SD_DAT0: J2.7 (DAT0), R28.1, U1.M19 (PF1)
/SD_DAT1: J2.8 (DAT1), R27.1, U1.M20 (PF0)
/SD_DAT2: J2.1 (DAT2), R31.1, U1.K19 (PF5)
/SD_DAT3: J2.2 (DAT3/CD), R30.1, U1.K20 (PF4)
/SD_DET: J2.9 (DET_B), R23.2, U1.B6 (PH1)
/UART_RX: J3.2, U1.B7 (PB23)
/UART_TX: J3.3, U1.A7 (PB22)
/USB_DN0: J1.A7 (D-), J1.B7 (D-), U1.N20 (DM0)
/USB_DN1: J6.2, U1.P20 (DM1)
/USB_DN2: J6.17, U1.R20 (DM2)
/USB_DP0: J1.A6 (D+), J1.B6 (D+), U1.N21 (DP0)
/USB_DP1: J6.3, U1.P21 (DP1)
/USB_DP2: J6.18, U1.R21 (DP2)
/XIN: C4.1, U1.N23 (X24MI), Y1.3
/XOUT: C5.1, U1.N22 (X24MO), Y1.1
GND: C1.2, C2.1, C3.1, C4.2, C5.2, C6.2, C7.2, C8.2, C9.2, C10.2, C11.2, C12.2, C13.2, C14.2, C15.2, C16.2, C17.2, C21.1, C23.1, C24.1, C25.1, C27.1, C28.1, C29.2, C30.2, C31.2, C32.2, C33.2, C34.2, C35.2, C36.2, C37.2, C38.2, C39.2, C40.2, C41.2, C42.2, C43.2, C44.2, C45.2, C46.2, C47.2, C48.2, C49.2, C50.2, C51.2, C52.2, C53.1, C54.2, C55.2, C56.2, C57.2, C60.2, C61.2, C70.1, C72.1, C73.1, C75.1, C76.1, C77.1, C79.1, C80.1, C82.1, C83.1, C84.1, C85.1, C86.1, D1.1 (K), D2.1 (K), J1.A1 (GND), J1.A12 (GND), J1.B1 (GND), J1.B12 (GND), J1.S1 (SHIELD), J2.6 (VSS), J2.10 (DET_A), J2.11 (SHIELD), J3.1, J5.7, J6.1, J6.4, J6.5, J6.6, J6.16, J6.25, J6.26, J6.27, J6.28, J6.29, J6.30, R2.2, R3.2, R4.2, R5.2, R6.2, R8.2, R10.2, R12.2, R16.2, R18.2, R26.1, U1.AA18 (GND), U1.G3 (GND), U1.G4 (GND), U1.J5 (GND), U1.J11 (GND), U1.K5 (GND), U1.K11 (GND), U1.K12 (GND), U1.K13 (GND), U1.K14 (GND), U1.L10 (GND), U1.L11 (GND), U1.L12 (GND)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
unnamed: D1.2 (A), R21.1
unnamed: D2.2 (A), R22.1
unnamed: J1.A5 (CC1), R3.1
unnamed: J1.B5 (CC2), R4.1
unnamed: R5.1, U1.AA7 (SZQ)
unnamed: R20.2, U1.W8 (BOOTSEL)
unnamed: R26.2, U1.T10 (JTAGSEL)
unnamed: R24.2, U1.F5 (NMI#)
unnamed: C17.1, U1.R15 (PLLVREG)
unnamed: R25.1, U1.C14 (RESET#), U9.2 (~RESET)
unnamed: R2.1, U2.L8 (ZQ0)
unnamed: C26.1, R7.2, R8.1, U3.5 (FB)
unnamed: L1.1, U3.3 (LX)
unnamed: C71.1, R9.2, R10.1, U4.5 (FB)
unnamed: L2.1, U4.3 (LX)
unnamed: C78.1, R11.2, R12.1, U5.5 (FB)
unnamed: L3.1, U5.3 (LX)
unnamed: C22.1, R1.2, R6.1, U8.5 (FB)
unnamed: L4.1, U8.3 (LX)
unnamed: R32.2, U9.3 (~MR)

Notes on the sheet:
CPU Power
Revision History
DDR3 DRAM
Micro SD
JTAG
CPU Configuration/XTAL
Power tree | 5v -> [D]3.3v [D]1.5v [D]1.2v-cpu [D]1.2v-sys [L]2.5v [L]1.3v
USB/UART/LED
EXT IO
CPU IO
Hypericum Release v1r0 APPROVAL 2023.7.3 1. corrected SDIO pull-ups 2. added silkscreen for extension interface
Hypericum Release v1r1 APPROVAL 2023.7.21 1. applied extension interface "SlimARM ExtIO" 2. use reset chip for cpu reset
Power -> DC-DC/LDO

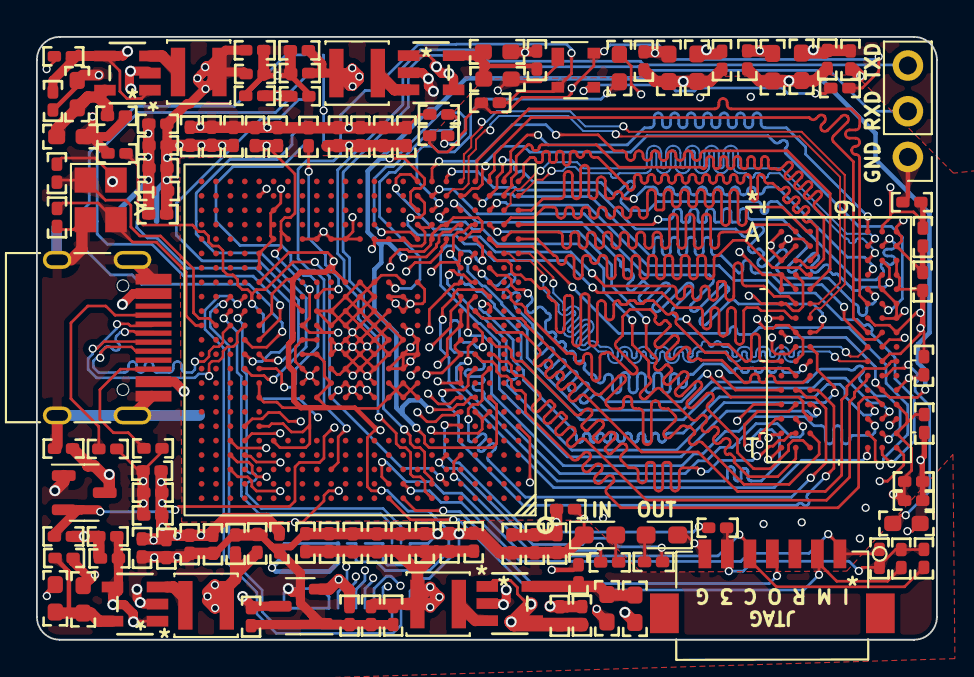
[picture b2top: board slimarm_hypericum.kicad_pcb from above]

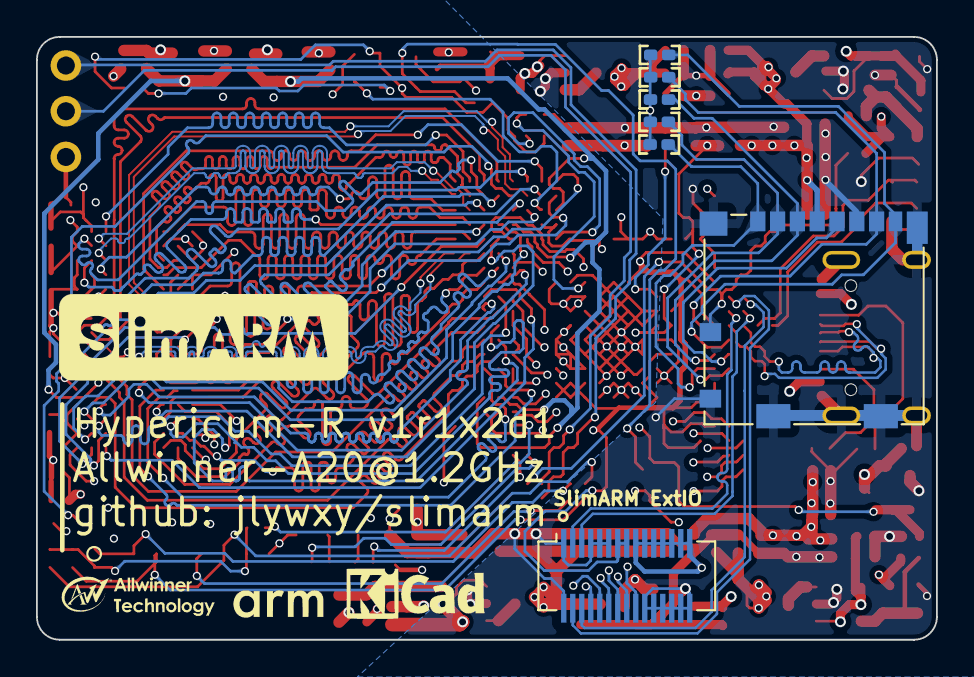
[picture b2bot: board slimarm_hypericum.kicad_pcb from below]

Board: 4 copper layers, 50.0 x 33.5 mm, 126 parts (7 on the bottom side), 108 nets.

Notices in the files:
parts and their libraries:
Copyright 2021 Accelerated Designs. All rights reserved.
